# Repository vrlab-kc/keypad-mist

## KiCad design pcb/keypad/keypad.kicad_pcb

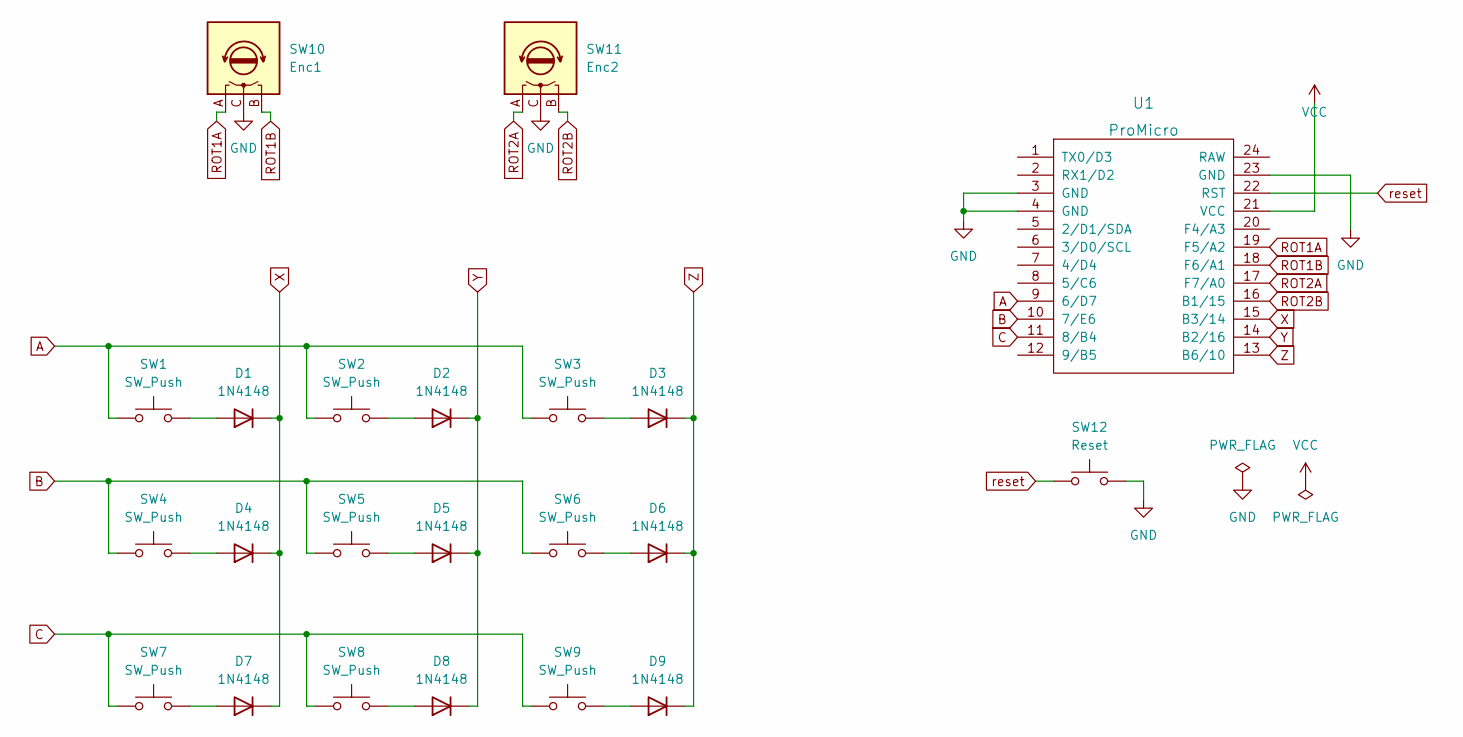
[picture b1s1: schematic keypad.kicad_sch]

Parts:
D1, D2, D3, D4, D5, D6, D7, D8, D9: 1N4148; D_DO-35_SOD27_P7.62mm_Horizontal
SW1, SW2, SW3, SW4, SW5, SW6, SW7, SW8, SW9: SW_Push; CherryMX_1u
SW10: Enc1; RotaryEncoder_Alps_EC12E_Vertical_H20mm_CircularMountingHol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
SW11: Enc2; RotaryEncoder_Alps_EC12E_Vertical_H20mm_CircularMountingHol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
SW12: Reset; SW_PUSH_6mm
U1: ProMicro; ProMicro_v3.5

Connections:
A: SW1.1, SW2.1, SW3.1, U1.9 (6/D7)
B: SW4.1, SW5.1, SW6.1, U1.10 (7/E6)
C: SW7.1, SW8.1, SW9.1, U1.11 (8/B4)
unnamed: D1.2 (A), SW1.2
unnamed: D2.2 (A), SW2.2
unnamed: D3.2 (A), SW3.2
unnamed: D4.2 (A), SW4.2
unnamed: D5.2 (A), SW5.2
unnamed: D6.2 (A), SW6.2
unnamed: D7.2 (A), SW7.2
unnamed: D8.2 (A), SW8.2
unnamed: D9.2 (A), SW9.2
ROT1A: SW10.A, U1.19 (F5/A2)
ROT1B: SW10.B, U1.18 (F6/A1)
ROT2A: SW11.A, U1.17 (F7/A0)
ROT2B: SW11.B, U1.16 (B1/15)
VCC: U1.21 (VCC)
X: D1.1 (K), D4.1 (K), D7.1 (K), U1.15 (B3/14)
Y: D2.1 (K), D5.1 (K), D8.1 (K), U1.14 (B2/16)
Z: D3.1 (K), D6.1 (K), D9.1 (K), U1.13 (B6/10)
reset: SW12.1, U1.22 (RST)

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
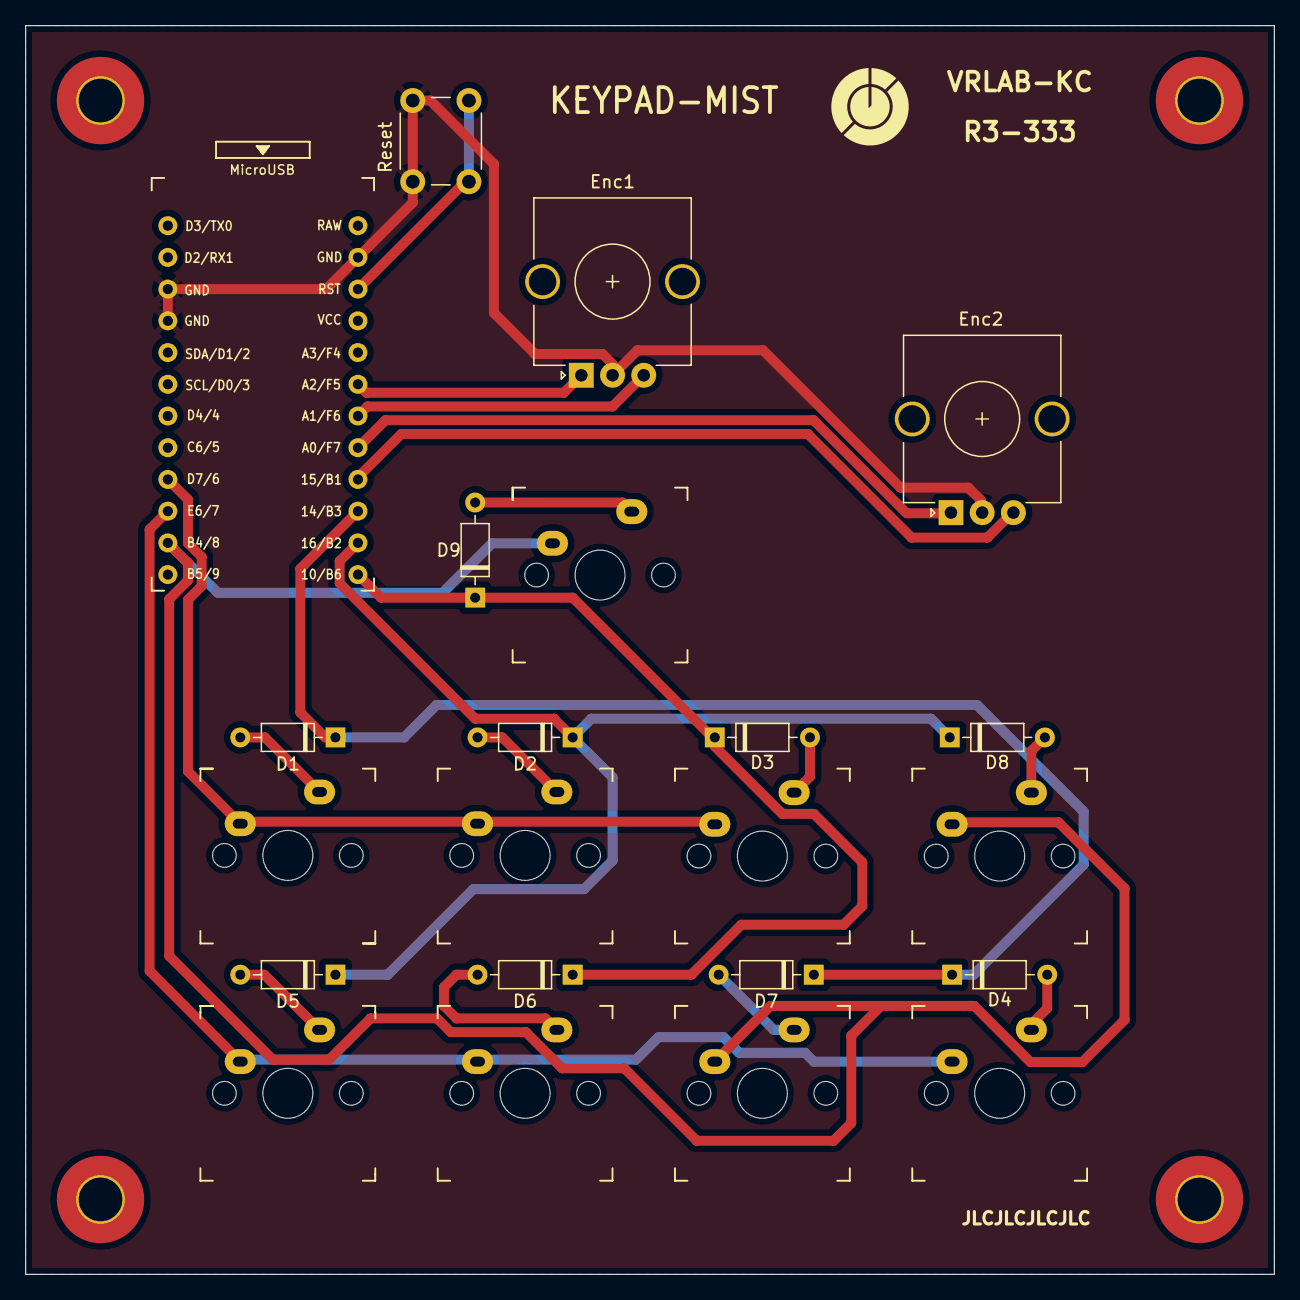
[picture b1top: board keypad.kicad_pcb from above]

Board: 2 copper layers, 100.0 x 100.0 mm, 23 parts (0 on the bottom side), 21 nets.

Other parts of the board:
REF: MountingHole_3.5mm_Pad_TopBottom

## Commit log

2023-03-15 追加 keySample
2023-03-15 修正 gitignore
    DS_Storeの誤字を修正
2023-03-27 追加 kicadファイル
2023-03-27 更新 kicad
2023-03-30 変更 pcb
2023-04-05 更新 firmware
2023-04-10 更新 pcb
2023-04-12 修正 firmware
2023-04-12 追加 DiyKeypadListener
2023-04-14 削除 DiyKeypadListener
